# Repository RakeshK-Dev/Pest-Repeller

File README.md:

# Pest-Repeller
The purpose of the project is to design an ultrasonic pest repellent. Such a device can be very useful to counter the various problems caused by ants, insects, pests, rodents, etc.I have also created the PCB for this device and included all the GERBER files here

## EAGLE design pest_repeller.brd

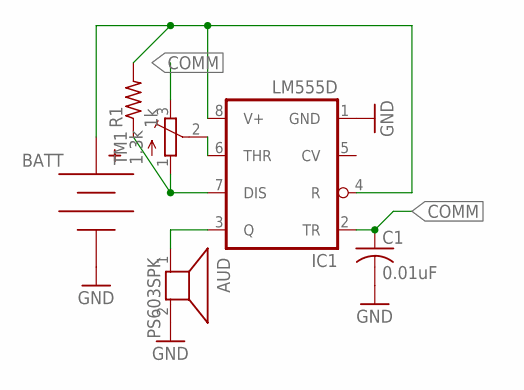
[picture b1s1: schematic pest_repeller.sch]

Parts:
AUD: PS603SPK; PS603; MPN MCKPSP2950PN-16/0.25A-4763
BATT: BC9VPC; MPN 96
C1: 0.01uF; C0805; MPN C0805J103K3RACAUTO
IC1: LM555D; SO08; MPN TLC555CP
R1: 1k; R0805; MPN CR0805-FX-1001ELF
TM1: 1.3k; TC33X; MPN 3306F-1-103

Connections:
COMM: C1.1, IC1.2 (TR), TM1.3 (E)
GND: AUD.2, BATT.V-, C1.2, IC1.1 (GND)
unnamed: BATT.V+, IC1.4 (R), IC1.8 (V+), R1.2
unnamed: IC1.7 (DIS), R1.1, TM1.1 (A)
unnamed: AUD.1, IC1.3 (Q)
unnamed: IC1.6 (THR), TM1.2 (S)

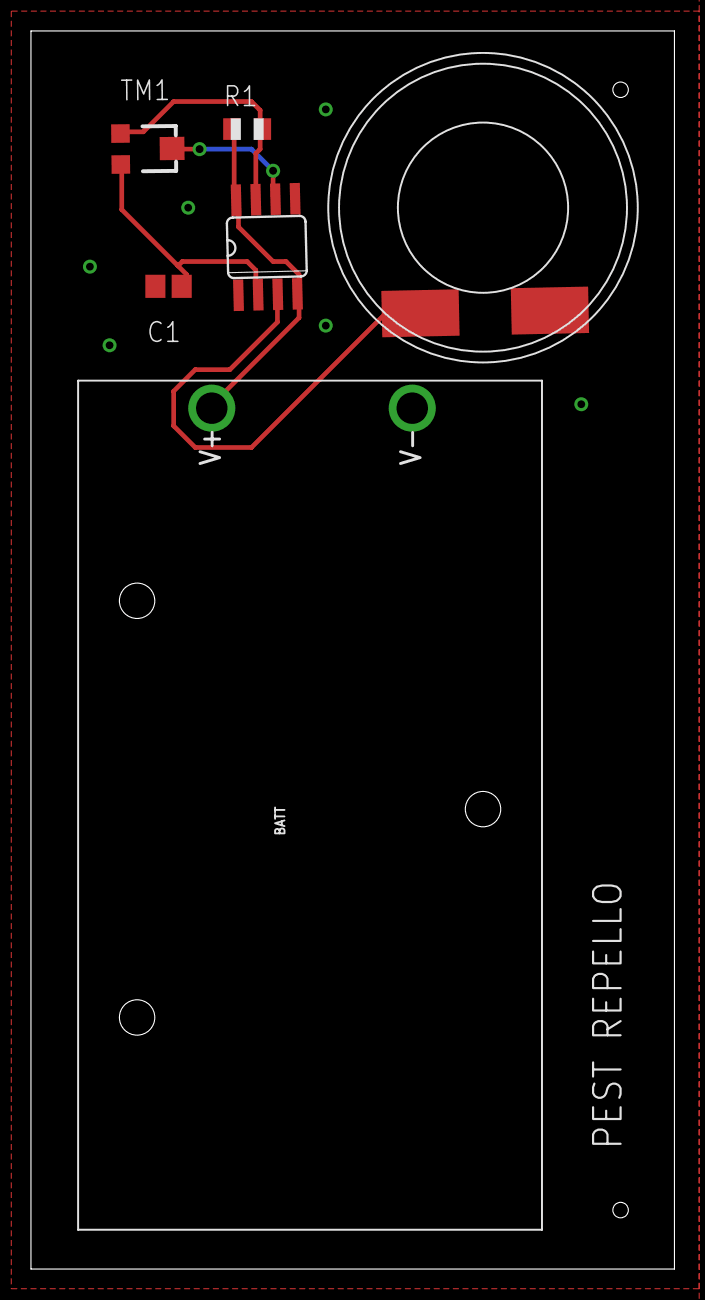
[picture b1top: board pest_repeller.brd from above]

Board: 2 copper layers, 41.6 x 80.0 mm, 6 parts (0 on the bottom side), 6 nets.

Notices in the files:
parts and their libraries:
SparkFun-Connectors: Licensing: Creative Commons ShareAlike 4.0 International - https://creativecommons.org/licenses/by-sa/4.0
